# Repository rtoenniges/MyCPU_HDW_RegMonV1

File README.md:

# MyCPU_HDW_RegMonV1

This little extension is a "live-display" for the register-set of the [MyCPU](http://www.mycpu.eu/).
The display shows the 16-bit wide address register, the 8-bit wide accumulator, X- and Y-register and stackpointer, and the three flags "overflow", "zero" and "carry".

The display board is layed out as piggyback for the CPU itself. The board is connected to the CPU either with flat cables or (with a bit tinkering) with long wirewrap-connectors. 
Because of this the display board is not suited for rack mount of the MyCPU system.

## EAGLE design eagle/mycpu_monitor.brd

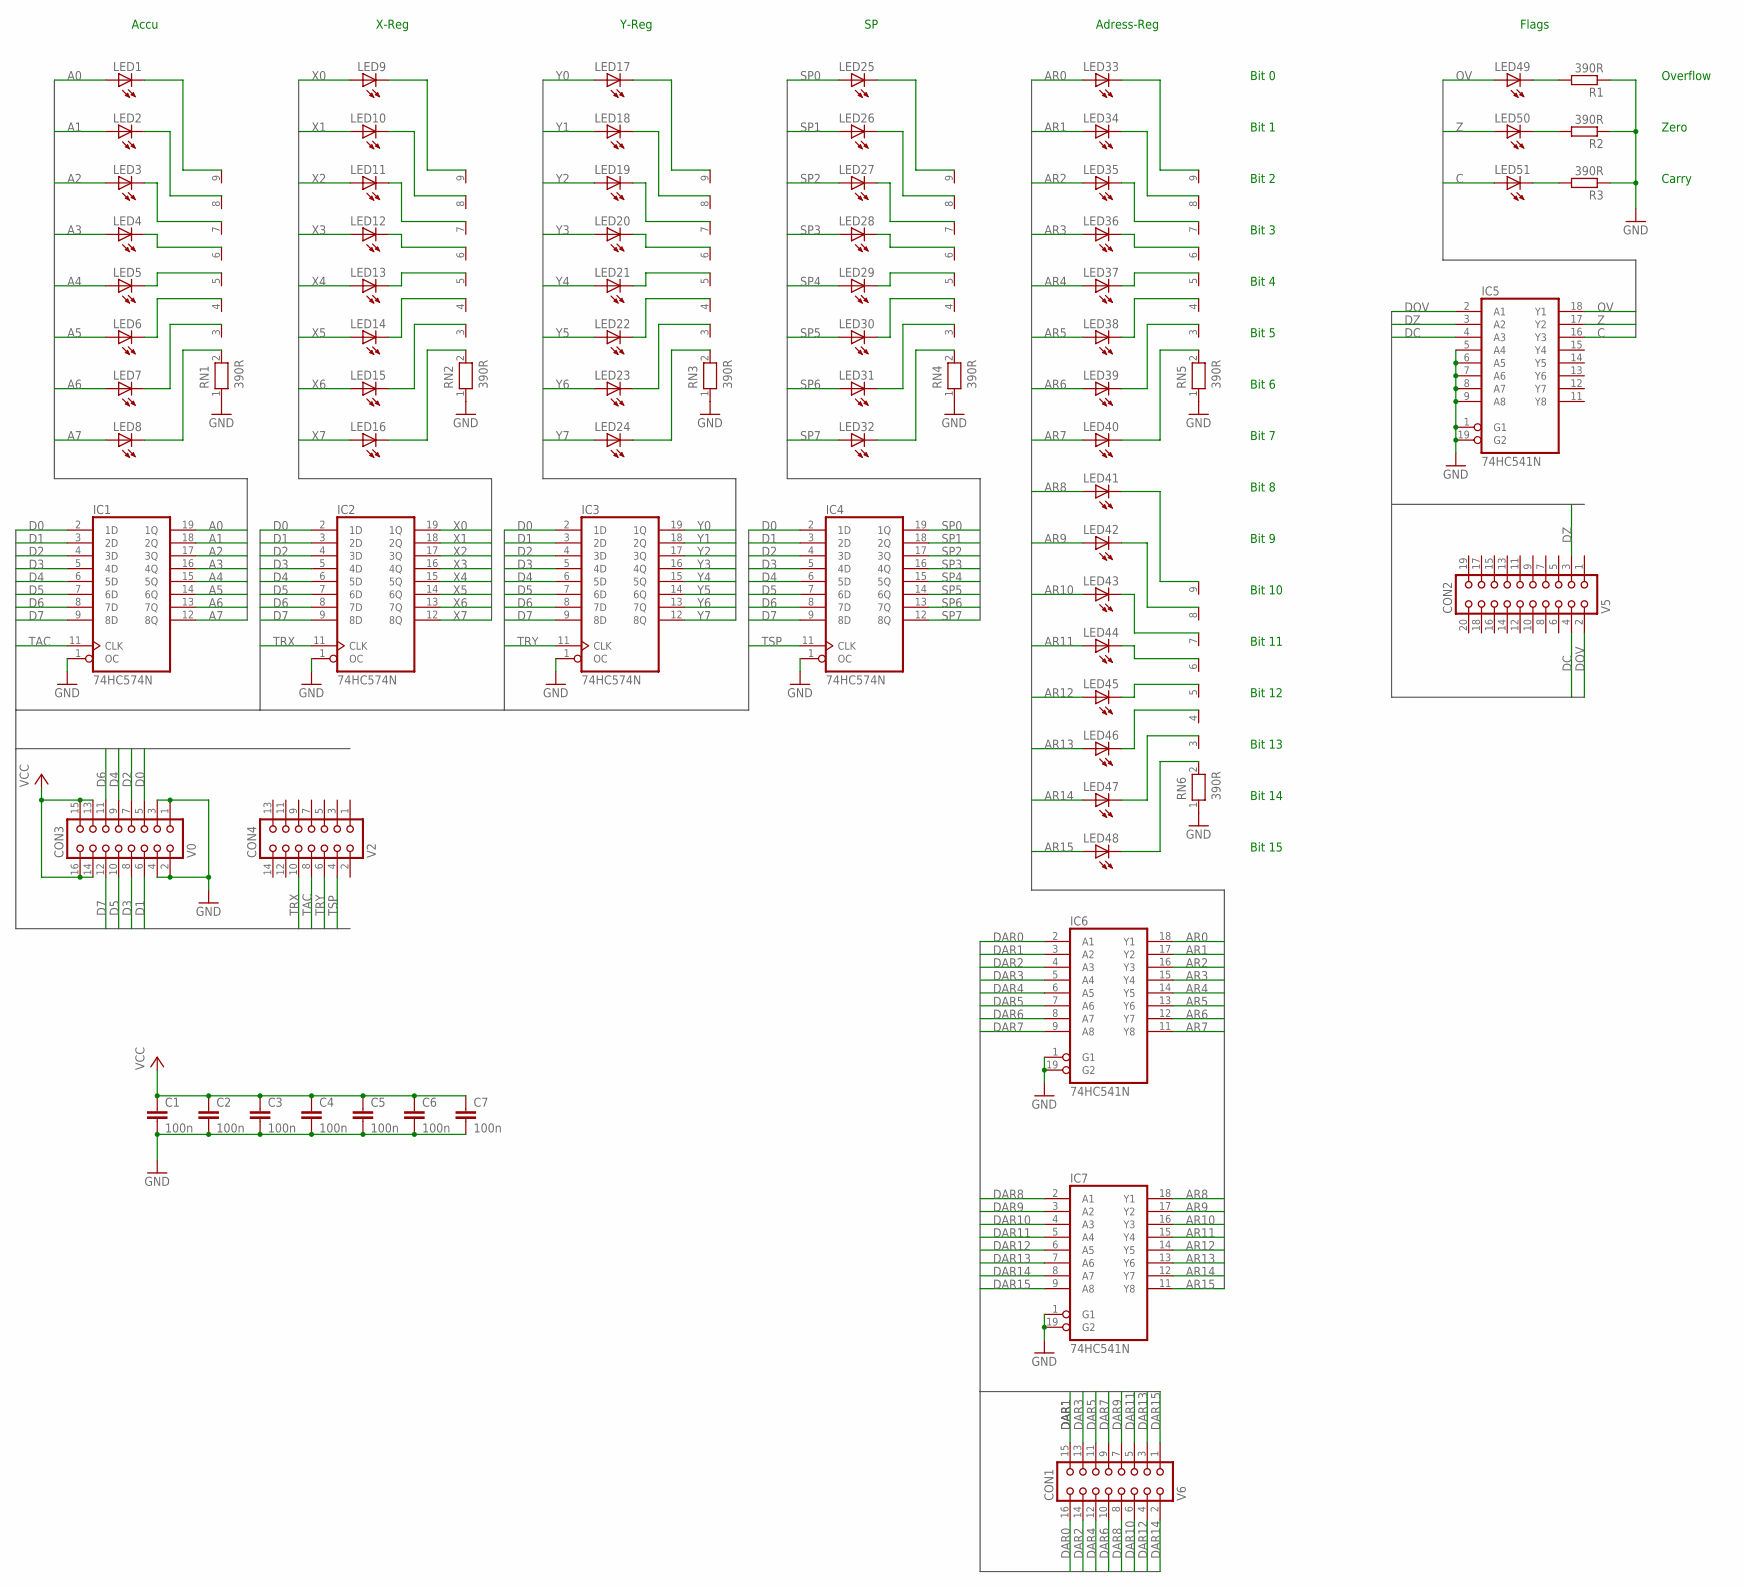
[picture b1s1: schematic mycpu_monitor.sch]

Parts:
C1, C2, C3, C4, C5, C6, C7: 100n; C050-024X044
CON1: V6; CON16L
CON2: V5; CON20L
CON3: V0; CON16L
CON4: V2; CON14L
IC1, IC2, IC3, IC4: 74HC574N; DIL20
IC5, IC6, IC7: 74HC541N; DIL20
LED1, LED2, LED3, LED4, LED5, LED6, LED7, LED8, LED9, LED10, LED11, LED12, LED13, LED14, LED15, LED16, LED17, LED18, LED19, LED20, LED21, LED22, LED23, LED24, LED25, LED26, LED27, LED28, LED29, LED30, LED31, LED32, LED33, LED34, LED35, LED36, LED37, LED38, LED39, LED40, LED41, LED42, LED43, LED44, LED45, LED46, LED47, LED48, LED49, LED50, LED51: LED3MM
R1, R2, R3: 390R; 0207/7
RN1, RN2, RN3, RN4, RN5, RN6: 390R; RN-9

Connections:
A0: IC1.19 (1Q), LED1.A
A1: IC1.18 (2Q), LED2.A
A2: IC1.17 (3Q), LED3.A
A3: IC1.16 (4Q), LED4.A
A4: IC1.15 (5Q), LED5.A
A5: IC1.14 (6Q), LED6.A
A6: IC1.13 (7Q), LED7.A
A7: IC1.12 (8Q), LED8.A
AR0: IC6.18 (Y1), LED33.A
AR1: IC6.17 (Y2), LED34.A
AR2: IC6.16 (Y3), LED35.A
AR3: IC6.15 (Y4), LED36.A
AR4: IC6.14 (Y5), LED37.A
AR5: IC6.13 (Y6), LED38.A
AR6: IC6.12 (Y7), LED39.A
AR7: IC6.11 (Y8), LED40.A
AR8: IC7.18 (Y1), LED41.A
AR9: IC7.17 (Y2), LED42.A
AR10: IC7.16 (Y3), LED43.A
AR11: IC7.15 (Y4), LED44.A
AR12: IC7.14 (Y5), LED45.A
AR13: IC7.13 (Y6), LED46.A
AR14: IC7.12 (Y7), LED47.A
AR15: IC7.11 (Y8), LED48.A
C: IC5.16 (Y3), LED51.A
D0: CON3.5, IC1.2 (1D), IC2.2 (1D), IC3.2 (1D), IC4.2 (1D)
D1: CON3.6, IC1.3 (2D), IC2.3 (2D), IC3.3 (2D), IC4.3 (2D)
D2: CON3.7, IC1.4 (3D), IC2.4 (3D), IC3.4 (3D), IC4.4 (3D)
D3: CON3.8, IC1.5 (4D), IC2.5 (4D), IC3.5 (4D), IC4.5 (4D)
D4: CON3.9, IC1.6 (5D), IC2.6 (5D), IC3.6 (5D), IC4.6 (5D)
D5: CON3.10, IC1.7 (6D), IC2.7 (6D), IC3.7 (6D), IC4.7 (6D)
D6: CON3.11, IC1.8 (7D), IC2.8 (7D), IC3.8 (7D), IC4.8 (7D)
D7: CON3.12, IC1.9 (8D), IC2.9 (8D), IC3.9 (8D), IC4.9 (8D)
DAR0: CON1.16, IC6.2 (A1)
DAR1: CON1.15, IC6.3 (A2)
DAR2: CON1.14, IC6.4 (A3)
DAR3: CON1.13, IC6.5 (A4)
DAR4: CON1.12, IC6.6 (A5)
DAR5: CON1.11, IC6.7 (A6)
DAR6: CON1.10, IC6.8 (A7)
DAR7: CON1.9, IC6.9 (A8)
DAR8: CON1.8, IC7.2 (A1)
DAR9: CON1.7, IC7.3 (A2)
DAR10: CON1.6, IC7.4 (A3)
DAR11: CON1.5, IC7.5 (A4)
DAR12: CON1.4, IC7.6 (A5)
DAR13: CON1.3, IC7.7 (A6)
DAR14: CON1.2, IC7.8 (A7)
DAR15: CON1.1, IC7.9 (A8)
DC: CON2.4, IC5.4 (A3)
DOV: CON2.2, IC5.2 (A1)
DZ: CON2.3, IC5.3 (A2)
GND: C1.2, C2.2, C3.2, C4.2, C5.2, C6.2, C7.2, CON3.1, CON3.2, CON3.3, CON3.4, IC1.1 (OC), IC1.10 (GND), IC2.1 (OC), IC2.10 (GND), IC3.1 (OC), IC3.10 (GND), IC4.1 (OC), IC4.10 (GND), IC5.1 (G1), IC5.5 (A4), IC5.6 (A5), IC5.7 (A6), IC5.8 (A7), IC5.9 (A8), IC5.10 (GND), IC5.19 (G2), IC6.1 (G1), IC6.10 (GND), IC6.19 (G2), IC7.1 (G1), IC7.10 (GND), IC7.19 (G2), R1.1, R2.1, R3.1, RN1.1, RN2.1, RN3.1, RN4.1, RN5.1, RN6.1
unnamed: LED8.K (C), RN1.2
unnamed: LED7.K (C), RN1.3
unnamed: LED6.K (C), RN1.4
unnamed: LED5.K (C), RN1.5
unnamed: LED4.K (C), RN1.6
unnamed: LED3.K (C), RN1.7
unnamed: LED2.K (C), RN1.8
unnamed: LED1.K (C), RN1.9
unnamed: LED16.K (C), RN2.2
unnamed: LED15.K (C), RN2.3
unnamed: LED14.K (C), RN2.4
unnamed: LED13.K (C), RN2.5
unnamed: LED12.K (C), RN2.6
unnamed: LED11.K (C), RN2.7
unnamed: LED10.K (C), RN2.8
unnamed: LED9.K (C), RN2.9
unnamed: LED24.K (C), RN3.2
unnamed: LED23.K (C), RN3.3
unnamed: LED22.K (C), RN3.4
unnamed: LED21.K (C), RN3.5
unnamed: LED20.K (C), RN3.6
unnamed: LED19.K (C), RN3.7
unnamed: LED18.K (C), RN3.8
unnamed: LED17.K (C), RN3.9
unnamed: LED32.K (C), RN4.2
unnamed: LED31.K (C), RN4.3
unnamed: LED30.K (C), RN4.4
unnamed: LED29.K (C), RN4.5
unnamed: LED28.K (C), RN4.6
unnamed: LED27.K (C), RN4.7
unnamed: LED26.K (C), RN4.8
unnamed: LED25.K (C), RN4.9
unnamed: LED40.K (C), RN5.2
unnamed: LED39.K (C), RN5.3
unnamed: LED38.K (C), RN5.4
unnamed: LED37.K (C), RN5.5
unnamed: LED36.K (C), RN5.6
unnamed: LED35.K (C), RN5.7
unnamed: LED34.K (C), RN5.8
unnamed: LED33.K (C), RN5.9
unnamed: LED48.K (C), RN6.2
unnamed: LED47.K (C), RN6.3
unnamed: LED46.K (C), RN6.4
unnamed: LED45.K (C), RN6.5
unnamed: LED44.K (C), RN6.6
unnamed: LED43.K (C), RN6.7
unnamed: LED42.K (C), RN6.8
unnamed: LED41.K (C), RN6.9
unnamed: LED51.K (C), R3.2
unnamed: LED50.K (C), R2.2
unnamed: LED49.K (C), R1.2
OV: IC5.18 (Y1), LED49.A
SP0: IC4.19 (1Q), LED25.A
SP1: IC4.18 (2Q), LED26.A
SP2: IC4.17 (3Q), LED27.A
SP3: IC4.16 (4Q), LED28.A
SP4: IC4.15 (5Q), LED29.A
SP5: IC4.14 (6Q), LED30.A
SP6: IC4.13 (7Q), LED31.A
SP7: IC4.12 (8Q), LED32.A
TAC: CON4.8, IC1.11 (CLK)
TRX: CON4.10, IC2.11 (CLK)
TRY: CON4.6, IC3.11 (CLK)
TSP: CON4.4, IC4.11 (CLK)
VCC: C1.1, C2.1, C3.1, C4.1, C5.1, C6.1, C7.1, CON3.13, CON3.14, CON3.15, CON3.16, IC1.20 (VCC), IC2.20 (VCC), IC3.20 (VCC), IC4.20 (VCC), IC5.20 (VCC), IC6.20 (VCC), IC7.20 (VCC)
X0: IC2.19 (1Q), LED9.A
X1: IC2.18 (2Q), LED10.A
X2: IC2.17 (3Q), LED11.A
X3: IC2.16 (4Q), LED12.A
X4: IC2.15 (5Q), LED13.A
X5: IC2.14 (6Q), LED14.A
X6: IC2.13 (7Q), LED15.A
X7: IC2.12 (8Q), LED16.A
Y0: IC3.19 (1Q), LED17.A
Y1: IC3.18 (2Q), LED18.A
Y2: IC3.17 (3Q), LED19.A
Y3: IC3.16 (4Q), LED20.A
Y4: IC3.15 (5Q), LED21.A
Y5: IC3.14 (6Q), LED22.A
Y6: IC3.13 (7Q), LED23.A
Y7: IC3.12 (8Q), LED24.A
Z: IC5.17 (Y2), LED50.A

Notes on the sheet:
Accu
X-Reg
Y-Reg
Adress-Reg
Overflow
Zero
Carry
Flags
Bit 0
Bit 1
Bit 2
Bit 3
Bit 4
Bit 5
Bit 6
Bit 7
Bit 8
Bit 9
Bit 10
Bit 11
Bit 12
Bit 13
Bit 14
Bit 15

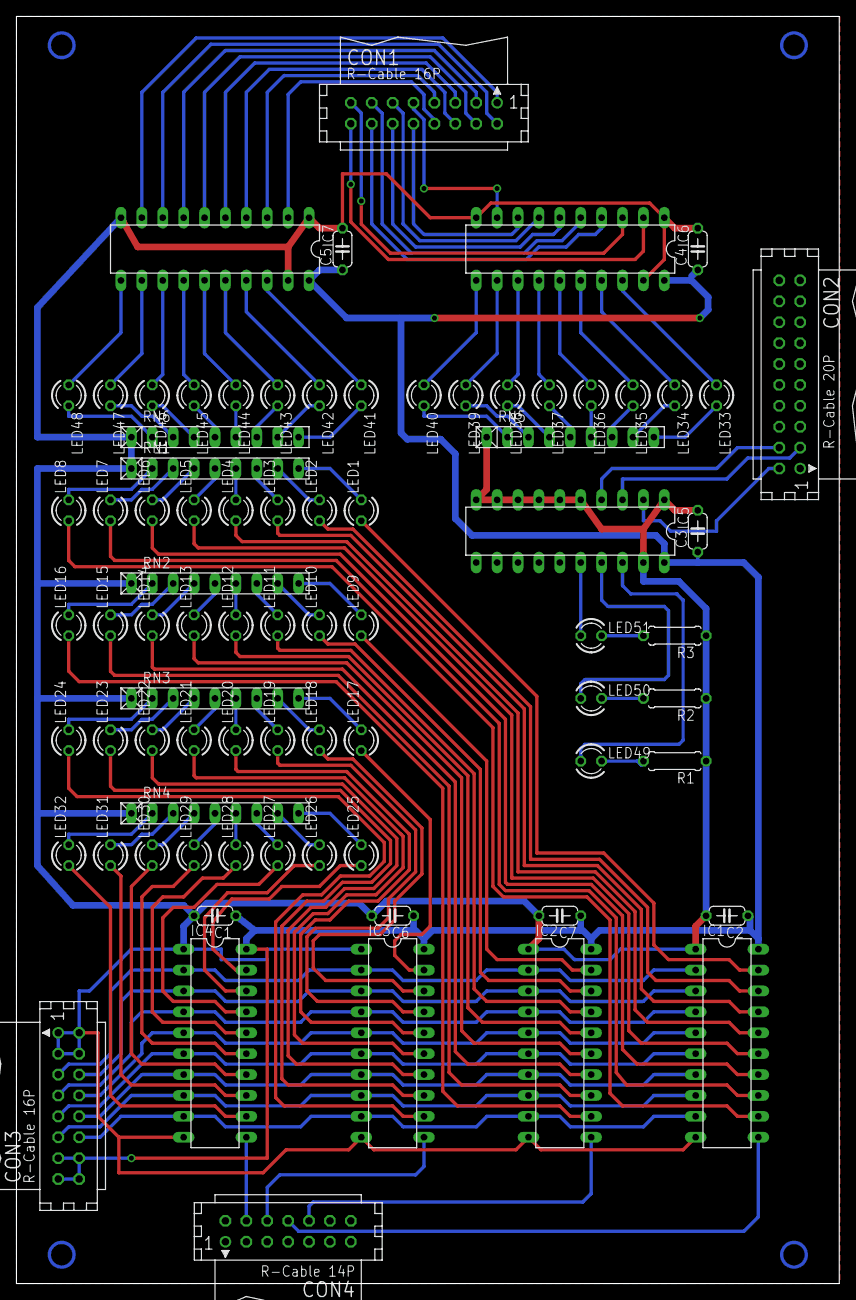
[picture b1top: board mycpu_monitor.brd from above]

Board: 2 copper layers, 100.0 x 154.0 mm, 78 parts (0 on the bottom side), 135 nets.

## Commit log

2017-03-20 Added licence
